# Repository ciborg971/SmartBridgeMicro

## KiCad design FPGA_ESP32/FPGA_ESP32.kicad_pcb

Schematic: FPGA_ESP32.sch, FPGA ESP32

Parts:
H1, H2, H3, H4: MountingHole_Pad; MountingHole_2.2mm_M2_Pad_Via
J1, J3, J4, J5: Conn_01x14_Female; PinHeader_1x14_P1.00mm_Vertical
R1, R2, R3, R4: 4K7; R_0201_0603Metric
U1: LFE5UM-25F-7MG285C; BGA285N50P18X18_1000X1000X130N

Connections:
+1V8: J5.2; also elsewhere on the board
/SPI_CLK: J5.8; also elsewhere on the board
/SPI_HD: J5.6; also elsewhere on the board
/SPI_MISO: J5.10; also elsewhere on the board
/SPI_MOSI: J5.9; also elsewhere on the board
/SPI_WP: J5.7; also elsewhere on the board
AVIN1: J1.2; also elsewhere on the board
AVIN2: J1.4; also elsewhere on the board
EN: J5.5; also elsewhere on the board
GND: H1.1, H2.1, H3.1, H4.1, J1.1, J1.3, J1.5, J3.2, J4.2, J5.1, J5.3; also elsewhere on the board
IO0: J1.6; also elsewhere on the board
IO1: J1.7; also elsewhere on the board
IO2: J1.8; also elsewhere on the board
IO3: J1.9; also elsewhere on the board
IO4: J1.10; also elsewhere on the board
IO5: J1.11; also elsewhere on the board
IO6: J1.12; also elsewhere on the board
IO7: J1.13; also elsewhere on the board
IO8: J1.14; also elsewhere on the board
IO9: J3.3; also elsewhere on the board
IO10: J3.4; also elsewhere on the board
IO11: J3.5; also elsewhere on the board
IO12: J3.6; also elsewhere on the board
IO13: J3.7; also elsewhere on the board
IO14: J3.8; also elsewhere on the board
IO15: J3.9; also elsewhere on the board
IO16: J3.10; also elsewhere on the board
IO17: J3.11; also elsewhere on the board
IO18: J3.12; also elsewhere on the board
IO19: J3.13; also elsewhere on the board
IO20: J3.14; also elsewhere on the board
IO21: J4.3; also elsewhere on the board
IO22: J4.4; also elsewhere on the board
IO23: J4.5; also elsewhere on the board
IO24: J4.6; also elsewhere on the board
IO25: J4.7; also elsewhere on the board
IO26: J4.8; also elsewhere on the board
IO27: J4.9; also elsewhere on the board
IO28: J4.10; also elsewhere on the board
IO29: J4.11; also elsewhere on the board
IO30: J4.12; also elsewhere on the board
IO31: J4.13, R2.1, U1.V13 (TMS); also elsewhere on the board
IO32: J4.14, R4.1, U1.V14 (TDO); also elsewhere on the board
IO33: J5.11; also elsewhere on the board
IO34: J5.12; also elsewhere on the board
IO35: J5.13; also elsewhere on the board
IO36: J5.14, R3.2, U1.T13 (TDI); also elsewhere on the board
IO37: R1.2, U1.U13 (TCK)
VIO: J3.1, J4.1, J5.4, R1.1, R2.2, R3.1, R4.2; also elsewhere on the board

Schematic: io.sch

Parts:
C1, C6, C14: 10uF; C_0402_1005Metric
C5, C11, C15, C16: 0.1uF; C_0402_1005Metric
C7, C17: C; C_0402_1005Metric
C19, C21: 1uF; C_0402_1005Metric
R5: 1M; R_0201_0603Metric
R7, R12, R13: 4.7K; R_0201_0603Metric
R14: 4K7; R_0201_0603Metric
U1: LFE5UM-25F-7MG285C; BGA285N50P18X18_1000X1000X130N
U3: LP5910-1.1BYKAT; BGA-4_2x2_0.74x0.74mm
U4, U6: W956D6KBKX; BGA-49_7x7_4.0x4.0mm
U5: TW9900; QFN-32_EP_4x4_Pitch0.4mm
U8: ADP222ACPZ-1825-R7; SON50P200X200X60-9N
Y1: Crystal_GND23; Crystal_SMD_2520-4Pin_2.5x2.0mm

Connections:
+1V8: C1.2, C5.2, C6.2, C11.2, C14.1, C15.1, U1.G5 (VCCIO2), U1.G14 (VCCIO7), U1.H5 (VCCIO2), U1.H14 (VCCIO7), U1.M14 (VCCIO6), U1.N14 (VCCIO6), U4.A1, U4.A3, U4.A5, U4.A7, U4.B4, U4.G3, U4.G5, U5.1, U5.7, U5.23, U6.A1, U6.A3, U6.A5, U6.A7, U6.B4, U6.G3, U6.G5, U8.7, U8.8; also elsewhere on the board
+2V5: U1.E6 (VCCAUX), U1.E13 (VCCAUX), U1.N6 (VCCAUX), U1.P5 (VCCAUXA0), U1.P13 (VCCAUX), U1.R3 (VCCAUXA0), U8.4, U8.5
/FPGA/DONE: U1.U15 (DONE); also elsewhere on the board
/FPGA/FPGA_CS: U1.R17 (PB13A/SN/CSN); also elsewhere on the board
/FPGA/FPGA_HOLDN: U1.U17 (PB15A/HOLDN/DI/BUSY/CSSPIN/CEN)
/FPGA/HSYNC: U1.A8 (PT35B/PCLKC1_0), U5.10
/FPGA/MPOUT: U1.N17 (PB6A/D5/MISO2/IO5), U5.11
/FPGA/RAM0_A16: U1.D18 (PL26C/PCLKT6_0), U4.G1
/FPGA/RAM0_A17: U1.F18 (PL26D/PCLKC6_0), U4.G7
/FPGA/RAM0_A18: U1.F17 (PL29A/GR_PCLK6_0), U4.F7
/FPGA/RAM0_A19: U1.F16 (PL29B), U4.E7
/FPGA/RAM0_A20: U1.F15 (PL29C/GR_PCLK6_1), U4.E1
/FPGA/RAM0_A21: U1.G16 (PL29D), U4.F1
/FPGA/RAM0_ADQ0: U1.G18 (PL32A), U4.B7
/FPGA/RAM0_ADQ1: U1.H17 (PL32B), U4.D7
/FPGA/RAM0_ADQ2: U1.G15 (PL35A), U4.C6
/FPGA/RAM0_ADQ3: U1.H15 (PL35B/VREF1_6), U4.C5
/FPGA/RAM0_ADQ4: U1.H16 (PL35C), U4.D4
/FPGA/RAM0_ADQ5: U1.J16 (PL35D), U4.B3
/FPGA/RAM0_ADQ6: U1.J18 (PL41A), U4.C2
/FPGA/RAM0_ADQ7: U1.K18 (PL41B), U4.D1
/FPGA/RAM0_ADQ8: U1.K16 (PL41C), U4.C7
/FPGA/RAM0_ADQ9: U1.K15 (PL41D), U4.B6
/FPGA/RAM0_ADQ10: U1.K17 (PL44A), U4.B5
/FPGA/RAM0_ADQ11: U1.L18 (PL44B), U4.D5
/FPGA/RAM0_ADQ12: U1.L15 (PL44C), U4.D3
/FPGA/RAM0_ADQ13: U1.L16 (PL44D), U4.C3
/FPGA/RAM0_ADQ14: U1.D17 (PL26A/PCLKT6_1), U4.B2
/FPGA/RAM0_ADQ15: U1.C18 (PL26B/PCLKC6_1), U4.C1
/FPGA/RAM0_ADV: U1.C12 (PL2A), U4.E2
/FPGA/RAM0_CE: U1.A15 (PL14D), U4.G6
/FPGA/RAM0_CLK: U1.B15 (PL20A/GR_PCLK7_1), U4.G2
/FPGA/RAM0_CRE: U1.D15 (PL17A), U4.F4
/FPGA/RAM0_LB: U1.A17 (PL23A/PCLKT7_1), U4.F6
/FPGA/RAM0_OE: U1.D16 (PL17B), U4.C4
/FPGA/RAM0_UB: U1.A12 (PL5A), U4.E6
/FPGA/RAM0_WAIT: U1.C13 (PL8B), U4.B1
/FPGA/RAM0_WE: U1.B12 (PL2B), U4.F2
/FPGA/RAM1_A16: U1.D1 (PR23D/PCLKC2_0), U6.G1
/FPGA/RAM1_A17: U1.D4 (PR14A), U6.G7
/FPGA/RAM1_A18: U1.C4 (PR14B), U6.F7
/FPGA/RAM1_A19: U1.B4 (PR14C/VREF1_2), U6.E7
/FPGA/RAM1_A20: U1.C3 (PR14D), U6.E1
/FPGA/RAM1_A21: U1.J17 (PL38C), U6.F1
/FPGA/RAM1_ADQ0: U1.A6 (PR11A), U6.B7
/FPGA/RAM1_ADQ1: U1.A4 (PR11B), U6.D7
/FPGA/RAM1_ADQ2: U1.B6 (PR8A), U6.C6
/FPGA/RAM1_ADQ3: U1.A7 (PR8B), U6.C5
/FPGA/RAM1_ADQ4: U1.D6 (PR5A), U6.D4
/FPGA/RAM1_ADQ5: U1.C6 (PR5B), U6.B3
/FPGA/RAM1_ADQ6: U1.C7 (PR2A), U6.C2
/FPGA/RAM1_ADQ7: U1.B7 (PR2B/S0_IN), U6.D1
/FPGA/RAM1_ADQ8: U1.D3 (PR17A), U6.C7
/FPGA/RAM1_ADQ9: U1.C2 (PR17B), U6.B6
/FPGA/RAM1_ADQ10: U1.A3 (PR20A/GR_PCLK2_1), U6.B5
/FPGA/RAM1_ADQ11: U1.B2 (PR20B), U6.D5
/FPGA/RAM1_ADQ12: U1.A2 (PR20C/GR_PCLK2_0), U6.D3
/FPGA/RAM1_ADQ13: U1.D2 (PR23A/PCLKT2_1), U6.C3
/FPGA/RAM1_ADQ14: U1.B1 (PR23B/PCLKC2_1), U6.B2
/FPGA/RAM1_ADQ15: U1.C1 (PR23C/PCLKT2_0), U6.C1
/FPGA/RAM1_ADV: U1.B13 (PL14A), U6.E2
/FPGA/RAM1_CE: U1.H18 (PL38D), U6.G6
/FPGA/RAM1_CLK: U1.C16 (PL20C/GR_PCLK7_0), U6.G2
/FPGA/RAM1_CRE: U1.D13 (PL8A), U6.F4
/FPGA/RAM1_LB: U1.M16 (PL47C/LLC_GPLL0T_IN), U6.F6
/FPGA/RAM1_OE: U1.A16 (PL20B), U6.C4
/FPGA/RAM1_UB: U1.M17 (PL47D/LLC_GPLL0C_IN), U6.E6
/FPGA/RAM1_WAIT: U1.C15 (PL14C/VREF1_7), U6.B1
/FPGA/RAM1_WE: U1.A13 (PL14B), U6.F2
/FPGA/TW_I2C_DAT: R13.1, U1.C8 (PT67B), U5.29
/FPGA/TW_I2C_SCK: R12.1, U1.B8 (PT67A), U5.28
/FPGA/TW_INT: U1.A9 (PT35A/PCLKT1_0), U5.32
/FPGA/TW_PWRDN: U1.C9 (PT33B/PCLKC1_1), U5.30
/FPGA/VIN_CLK: U1.A11 (PT27A/PCLKT0_1), U5.12
/FPGA/VIN_D0: U1.C10 (PT29B/PCLKC0_0), U5.22
/FPGA/VIN_D1: U1.B10 (PT29A/PCLKT0_0), U5.21
/FPGA/VIN_D2: U1.R18 (PB9B/D2/IO2), U5.20
/FPGA/VIN_D3: U1.N18 (PB9A/D3/IO3), U5.19
/FPGA/VIN_D4: U1.C11 (PT4B), U5.17
/FPGA/VIN_D5: U1.B11 (PT4A), U5.16
/FPGA/VIN_D6: U1.N16 (PB4B/D6/IO6), U5.15
/FPGA/VIN_D7: U1.N15 (PB4A/D7/IO7), U5.14
/FPGA/VSYNC: U1.M18 (PB6B/D4/MOSI2/IO4), U5.9
/FPGA/nRESET: U1.B9 (PT33A/PCLKT1_1), U5.31
/SPI_CLK: U1.U16 (CCLK/MCLK/SCK); also elsewhere on the board
/SPI_HD: U1.R16 (PB18A/WRITEN); also elsewhere on the board
/SPI_MISO: U1.T18 (PB11A/D1/MISO/IO1); also elsewhere on the board
/SPI_MOSI: U1.U18 (PB11B/D0/MOSI/IO0); also elsewhere on the board
/SPI_WP: U1.T17 (PB13B/CS1N); also elsewhere on the board
/WIFI, BT, RT/FPGA_PROGRAMN: U1.T15 (PROGRAMN); also elsewhere on the board
AVIN1: U5.3; also elsewhere on the board
AVIN2: U5.2; also elsewhere on the board
GND: C1.1, C5.1, C6.1, C7.2, C11.1, C14.2, C15.2, C16.2, C17.2, C19.2, C21.2, R5.1, R5.2, U1.B3 (GND), U1.B16 (GND), U1.E5 (GND), U1.E7 (GND), U1.E8 (GND), U1.E9 (GND), U1.E10 (GND), U1.E11 (GND), U1.E12 (GND), U1.E14 (GND), U1.F5 (GND), U1.F6 (GND), U1.F7 (GND), U1.F8 (GND), U1.F9 (GND), U1.F10 (GND), U1.F11 (GND), U1.F12 (GND), U1.F13 (GND), U1.F14 (GND), U1.G2 (GND), U1.G6 (GND), U1.G7 (GND), U1.G8 (GND), U1.G9 (GND), U1.G10 (GND), U1.G11 (GND), U1.G12 (GND), U1.G13 (GND), U1.G17 (GND), U1.H6 (GND), U1.H7 (GND), U1.H8 (GND), U1.H9 (GND), U1.H10 (GND), U1.H11 (GND), U1.H12 (GND), U1.H13 (GND), U1.J6 (GND), U1.J7 (GND), U1.J8 (GND), U1.J9 (GND), U1.J10 (GND), U1.J11 (GND), U1.J12 (GND), U1.J13 (GND), U1.K5 (GND), U1.K6 (GND), U1.K7 (GND), U1.K8 (GND), U1.K9 (GND), U1.K10 (GND), U1.K11 (GND), U1.K12 (GND), U1.K13 (GND), U1.K14 (GND), U1.L2 (GND), U1.L5 (GND), U1.L6 (GND), U1.L7 (GND), U1.L8 (GND), U1.L9 (GND), U1.L10 (GND), U1.L11 (GND), U1.L12 (GND), U1.L13 (GND), U1.L14 (GND), U1.L17 (GND), U1.M6 (GND), U1.M7 (GND), U1.M8 (GND), U1.M9 (GND), U1.M10 (GND), U1.M11 (GND), U1.M12 (GND), U1.M13 (GND), U1.N7 (GND), U1.N8 (GND), U1.N9 (GND), U1.N10 (GND), U1.N11 (GND), U1.N12 (GND), U1.P6 (GND), U1.P8 (GND), U1.P12 (GND), U1.R1 (GND), U1.R2 (GND), U1.T2 (GND), U1.T3 (GND), U1.T4 (GND), U1.T6 (GND), U1.T7 (GND), U1.T8 (GND), U1.T9 (GND), U1.T10 (GND), U1.T11 (GND), U1.T12 (GND), U1.T16 (GND), U1.U2 (GND), U1.U3 (GND), U1.U4 (GND), U1.U5 (GND), U1.U7 (GND), U1.U9 (GND), U1.U10 (GND), U1.U11 (GND), U1.U14 (CFG_0), U1.V4 (GND), U1.V7 (GND), U1.V10 (GND), U1.V15 (CFG_2), U3.B2, U4.A2, U4.A4, U4.A6, U4.D2, U4.D6, U4.E3, U4.E4, U4.E5, U4.G4, U5.4, U5.5, U5.8, U5.13, U5.24, U5.33, U6.A2, U6.A4, U6.A6, U6.D2, U6.D6, U6.E3, U6.E4, U6.E5, U6.G4, U8.3, U8.9, Y1.2, Y1.3; also elsewhere on the board
IO0: U1.F2 (PR32A); also elsewhere on the board
IO1: U1.G1 (PR32B); also elsewhere on the board
IO2: U1.M3 (PR41A); also elsewhere on the board
IO3: U1.L3 (PR41B); also elsewhere on the board
IO4: U1.K3 (PR41C); also elsewhere on the board
IO5: U1.K1 (PR41D); also elsewhere on the board
IO6: U1.K4 (PR38A); also elsewhere on the board
IO7: U1.L4 (PR38B); also elsewhere on the board
IO8: U1.N4 (PR38C); also elsewhere on the board
IO9: U1.N3 (PR38D); also elsewhere on the board
IO10: U1.K2 (PR44A); also elsewhere on the board
IO11: U1.L1 (PR44B); also elsewhere on the board
IO12: U1.M2 (PR44C); also elsewhere on the board
IO13: U1.N2 (PR44D); also elsewhere on the board
IO14: U1.J2 (PR35A); also elsewhere on the board
IO15: U1.J1 (PR35B/VREF1_3); also elsewhere on the board
IO16: U1.F1 (PR35C); also elsewhere on the board
IO17: U1.H1 (PR35D); also elsewhere on the board
IO18: U1.H3 (PR29A/GR_PCLK3_0); also elsewhere on the board
IO19: U1.G3 (PR29B); also elsewhere on the board
IO20: U1.J3 (PR29C/GR_PCLK3_1); also elsewhere on the board
IO21: U1.H2 (PR29D); also elsewhere on the board
IO22: U1.H4 (PR26A/PCLKT3_1); also elsewhere on the board
IO23: U1.G4 (PR26B/PCLKC3_1); also elsewhere on the board
IO24: U1.F4 (PR26C/PCLKT3_0); also elsewhere on the board
IO25: U1.B17 (PL23B/PCLKC7_1); also elsewhere on the board
IO26: U1.B18 (PL23C/PCLKT7_0); also elsewhere on the board
IO27: U1.C17 (PL23D/PCLKC7_0); also elsewhere on the board
unnamed: C7.1, U5.25, Y1.1
unnamed: C16.1, U5.6
unnamed: C17.1, U5.26, Y1.4
unnamed: R7.2, U1.V16 (INITN)
unnamed: R14.1, U1.T14 (CFG_1)
VIO: C19.1, R7.1, R12.2, R13.2, R14.2, U1.D7 (VCCIO1), U1.D12 (VCCIO0), U1.M5 (VCCIO3), U1.N5 (VCCIO3), U1.N13 (VCCIO8), U1.P14 (VCCIO8), U3.A1, U3.B1, U5.18, U5.27, U8.1, U8.2, U8.6; also elsewhere on the board

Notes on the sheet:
1V1 Reg
2V5 Reg
1V8 Reg

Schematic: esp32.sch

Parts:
C2, C3: 220pF; C_0402_1005Metric
C4: 2.2uF; C_0402_1005Metric
C8, C9, C18: 0.1uF; C_0402_1005Metric
C10: 1uF; C_0402_1005Metric
C12: 3.9pF; C_0402_1005Metric
C13: 2.4pF; C_0402_1005Metric
J2, J6: U_FL-R-SMT_10_; Coax_Conn_U.FL; MPN U.FL-R-SMT(10); Digi-Key_PN H9161CT-ND
L1: 1.2nH; L_0402_1005Metric
L2: 2.7N; L_0402_1005Metric
R6, R8: 10K; R_0201_0603Metric
R16, R17, R18, R19: 1K; R_0201_0603Metric
U2: ESP32-PICO-D4; QFN-48-1EP_7x7mm_P0.5mm_EP5.3x5.3mm
U7: RFX2411; QFN-20_EP_3x3_Pitch0.4mm
U10: GD25Q16CEIGR; PSON50P200X300X50-9N

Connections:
/FPGA/DONE: U2.17 (IO14); also elsewhere on the board
/FPGA/FPGA_CS: U2.18 (IO12); also elsewhere on the board
/SPI_CLK: U2.35 (IO18), U10.6; also elsewhere on the board
/SPI_HD: U2.42 (IO21); also elsewhere on the board
/SPI_MISO: U2.38 (IO19), U10.2; also elsewhere on the board
/SPI_MOSI: U2.36 (IO23), U10.5; also elsewhere on the board
/SPI_WP: U2.39 (IO22); also elsewhere on the board
/WIFI, BT, RT/FPGA_PROGRAMN: U2.21 (IO15); also elsewhere on the board
/WIFI, BT, RT/HOLD: U2.14 (IO25), U10.3
/WIFI, BT, RT/MODE: R17.2, U2.29 (SD3/IO10)
/WIFI, BT, RT/PDET: C9.1, R6.1, U2.8 (SENSOR_VN), U7.8
/WIFI, BT, RT/RXEN: R18.2, U2.12 (IO32)
/WIFI, BT, RT/SPI_FLASH_CS: U2.15 (IO26), U10.1
/WIFI, BT, RT/SWANT: R16.2, U2.28 (SD2/IO9)
/WIFI, BT, RT/TXEN: R19.2, U2.13 (IO33)
/WIFI, BT, RT/TXRX: C12.2, C13.1, U7.5
/WIFI, BT, RT/WP: U2.16 (IO27), U10.7
EN: C18.1, R8.2, U2.9 (EN); also elsewhere on the board
GND: C2.2, C3.2, C4.2, C8.2, C9.2, C10.2, C13.2, C18.2, J2.1, J6.1, L1.1, L2.2, R6.2, U2.49 (GND), U7.1, U7.11, U7.13, U7.19, U7.21, U10.4; also elsewhere on the board
IO28: U2.20 (IO13); also elsewhere on the board
IO29: U2.10 (IO34); also elsewhere on the board
IO30: U2.11 (IO35); also elsewhere on the board
IO31: U2.23 (IO0); also elsewhere on the board
IO32: U2.41 (U0TXD/IO1); also elsewhere on the board
IO33: U2.22 (IO2); also elsewhere on the board
IO34: U2.40 (U0RXD/IO3); also elsewhere on the board
IO35: U2.24 (IO4); also elsewhere on the board
IO36: U2.34 (IO5); also elsewhere on the board
unnamed: C12.1, L2.1, U2.2 (LNA_IN)
unnamed: J2.2, U7.14
unnamed: J6.2, U7.12
unnamed: L1.2, U7.15
unnamed: R16.1, U7.10
unnamed: R17.1, U7.9
unnamed: R18.1, U7.7
unnamed: R19.1, U7.6
VIO: C2.1, C3.1, C4.1, C8.1, C10.1, R8.1, U2.1 (VDDA), U2.3 (VDDA3P3), U2.4 (VDDA3P3), U2.19 (VDD3P3_RTC), U2.37 (VDD3P3_CPU), U2.43 (VDDA), U2.46 (VDDA), U7.18, U7.20, U10.8; also elsewhere on the board

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
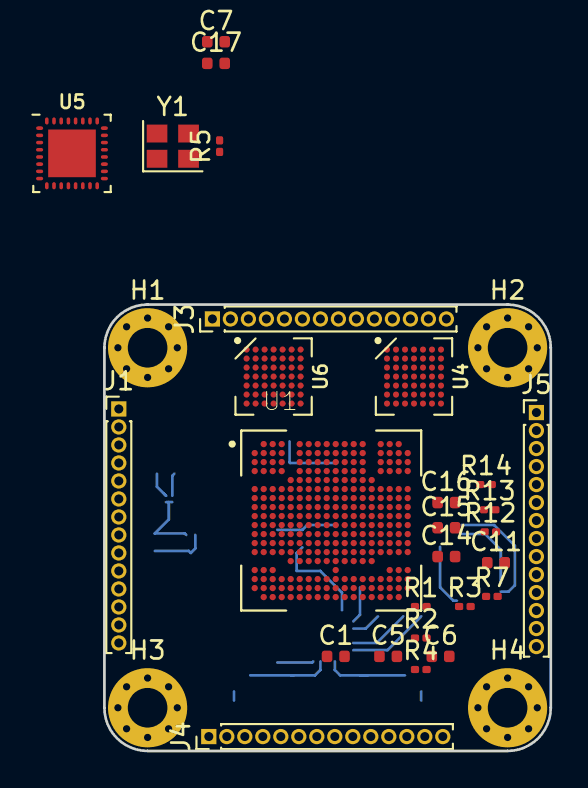
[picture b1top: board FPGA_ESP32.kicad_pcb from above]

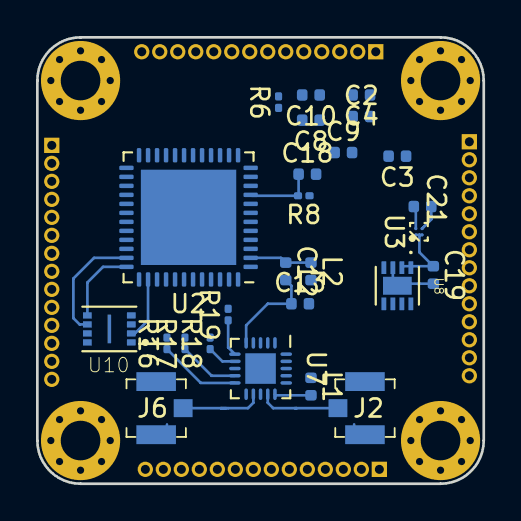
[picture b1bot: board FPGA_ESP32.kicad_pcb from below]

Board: 4 copper layers, 24.8 x 24.8 mm, 57 parts (26 on the bottom side), 155 nets.

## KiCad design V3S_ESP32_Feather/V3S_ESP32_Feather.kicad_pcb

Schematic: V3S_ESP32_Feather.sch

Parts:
J1: USB_B_Micro; JST_SH_BM05B-SRSS-TB_1x05-1MP_P1.00mm_Vertical
J10: UART; JST_SH_SM04B-SRSS-TB_1x04-1MP_P1.00mm_Horizontal
MH1, MH2, MH3, MH4: MountingHole_Pad; MountingHole_2.5mm_Pad_Via
TP4: CPU_RST; TestPoint_Pad_D1.0mm

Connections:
+3V3: J10.4; also elsewhere on the board
/RST: TP4.1; also elsewhere on the board
/UART_RX_D0: J10.2; also elsewhere on the board
/UART_TX_D0: J10.3; also elsewhere on the board
/USB_D_N: J1.3; also elsewhere on the board
/USB_D_P: J1.2; also elsewhere on the board
/USB_ID: J1.5; also elsewhere on the board
GND: J1.1, J10.1, MH1.1, MH2.1, MH3.1, MH4.1; also elsewhere on the board
VBUS: J1.4; also elsewhere on the board

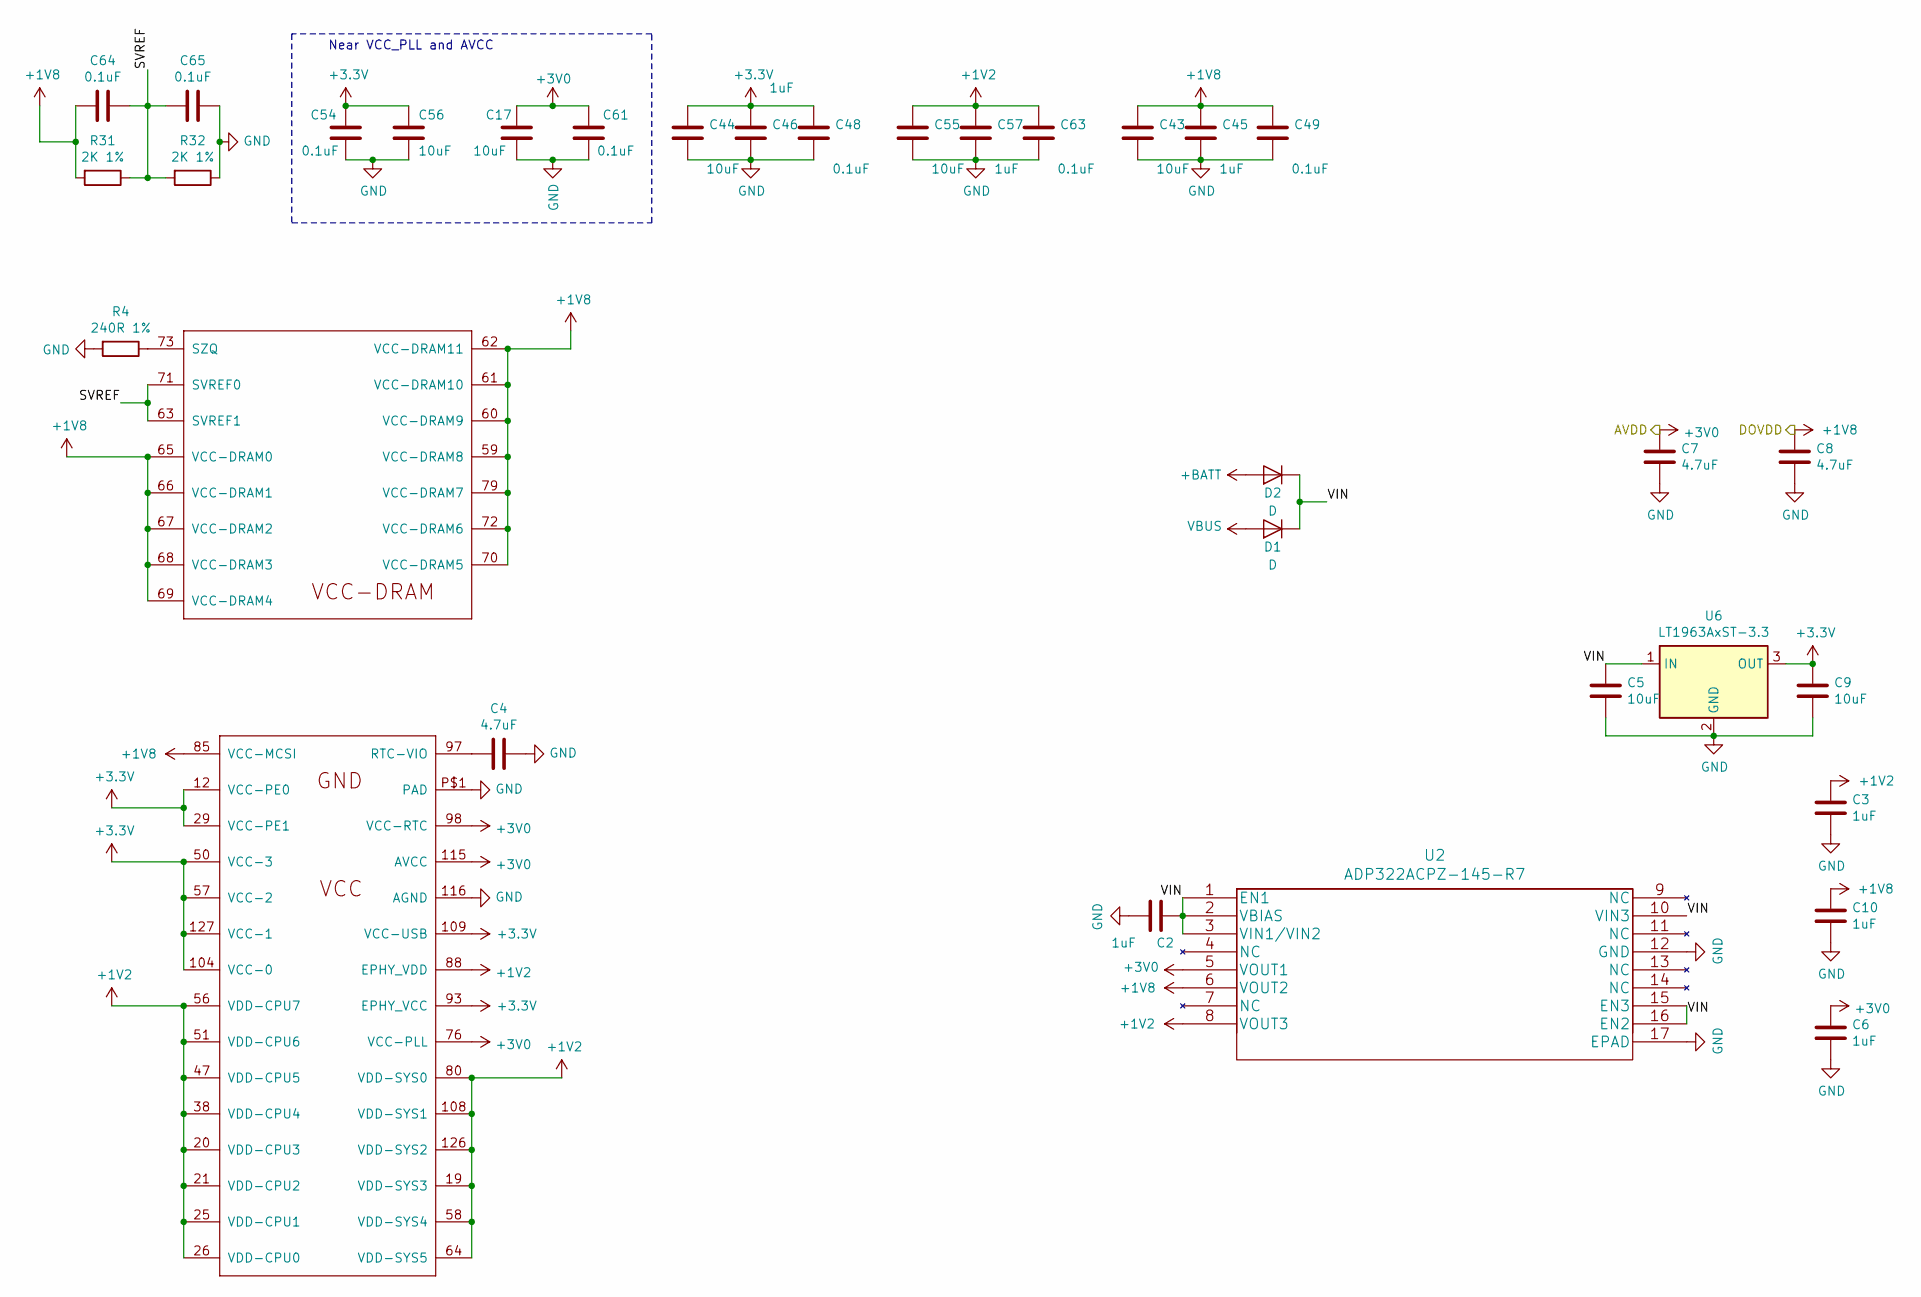
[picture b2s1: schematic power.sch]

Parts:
C2, C3, C6, C10, C45, C46, C57: 1uF; C_0201_0603Metric
C4, C7, C8: 4.7uF; C_0201_0603Metric
C5, C9, C17, C43, C44, C55, C56: 10uF; C_0402_1005Metric
C48, C49, C54, C61, C63, C64, C65: 0.1uF; C_0201_0603Metric
D1, D2: D; D_0201_0603Metric
R4: 240R 1%; R_0201_0603Metric
R31, R32: 2K 1%; R_0201_0603Metric
U1: V3S; LQFP-128_14x14mm_P0.4mm
U2: ADP322ACPZ-145-R7; QFN50P300X300X90-17N
U6: LT1963AxST-3.3; SOT-223-3_TabPin2

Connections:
+1V2: C3.1, C55.1, C57.1, C63.1, U1.19 (VDD-SYS3), U1.20 (VDD-CPU3), U1.21 (VDD-CPU2), U1.25 (VDD-CPU1), U1.26 (VDD-CPU0), U1.38 (VDD-CPU4), U1.47 (VDD-CPU5), U1.51 (VDD-CPU6), U1.56 (VDD-CPU7), U1.58 (VDD-SYS4), U1.64 (VDD-SYS5), U1.80 (VDD-SYS0), U1.88 (EPHY_VDD), U1.108 (VDD-SYS1), U1.126 (VDD-SYS2), U2.8 (VOUT3)
+1V8: C8.1, C10.1, C43.1, C45.1, C49.1, C64.2, R31.2, U1.59 (VCC-DRAM8), U1.60 (VCC-DRAM9), U1.61 (VCC-DRAM10), U1.62 (VCC-DRAM11), U1.65 (VCC-DRAM0), U1.66 (VCC-DRAM1), U1.67 (VCC-DRAM2), U1.68 (VCC-DRAM3), U1.69 (VCC-DRAM4), U1.70 (VCC-DRAM5), U1.72 (VCC-DRAM6), U1.79 (VCC-DRAM7), U1.85 (VCC-MCSI), U2.6 (VOUT2); also elsewhere on the board
+3V0: C6.1, C7.1, C17.2, C61.2, U1.76 (VCC-PLL), U1.98 (VCC-RTC), U1.115 (AVCC), U2.5 (VOUT1); also elsewhere on the board
+3V3: C9.1, C44.1, C46.1, C48.1, C54.1, C56.1, U1.12 (VCC-PE0), U1.29 (VCC-PE1), U1.50 (VCC-3), U1.57 (VCC-2), U1.93 (EPHY_VCC), U1.104 (VCC-0), U1.109 (VCC-USB), U1.127 (VCC-1), U6.3 (OUT); also elsewhere on the board
+BATT: D2.2 (A); also elsewhere on the board
/PMIC Power Battery/SVREF: C64.1, C65.2, R31.1, R32.2, U1.63 (SVREF1), U1.71 (SVREF0)
/PMIC Power Battery/VIN: C2.1, C5.1, D1.1 (K), D2.1 (K), U2.1 (EN1), U2.2 (VBIAS), U2.3 (VIN1/VIN2), U2.10 (VIN3), U2.15 (EN3), U2.16 (EN2), U6.1 (IN)
GND: C2.2, C3.2, C4.1, C5.2, C6.2, C7.2, C8.2, C9.2, C10.2, C17.1, C43.2, C44.2, C45.2, C46.2, C48.2, C49.2, C54.2, C55.2, C56.2, C57.2, C61.1, C63.2, C65.1, R4.2, R32.1, U1.116 (AGND), U1.P$1 (PAD), U2.12 (GND), U2.17 (EPAD), U6.2 (GND); also elsewhere on the board
unnamed: C4.2, U1.97 (RTC-VIO)
unnamed: R4.1, U1.73 (SZQ)
VBUS: D1.2 (A); also elsewhere on the board

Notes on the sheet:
Near VCC_PLL and AVCC

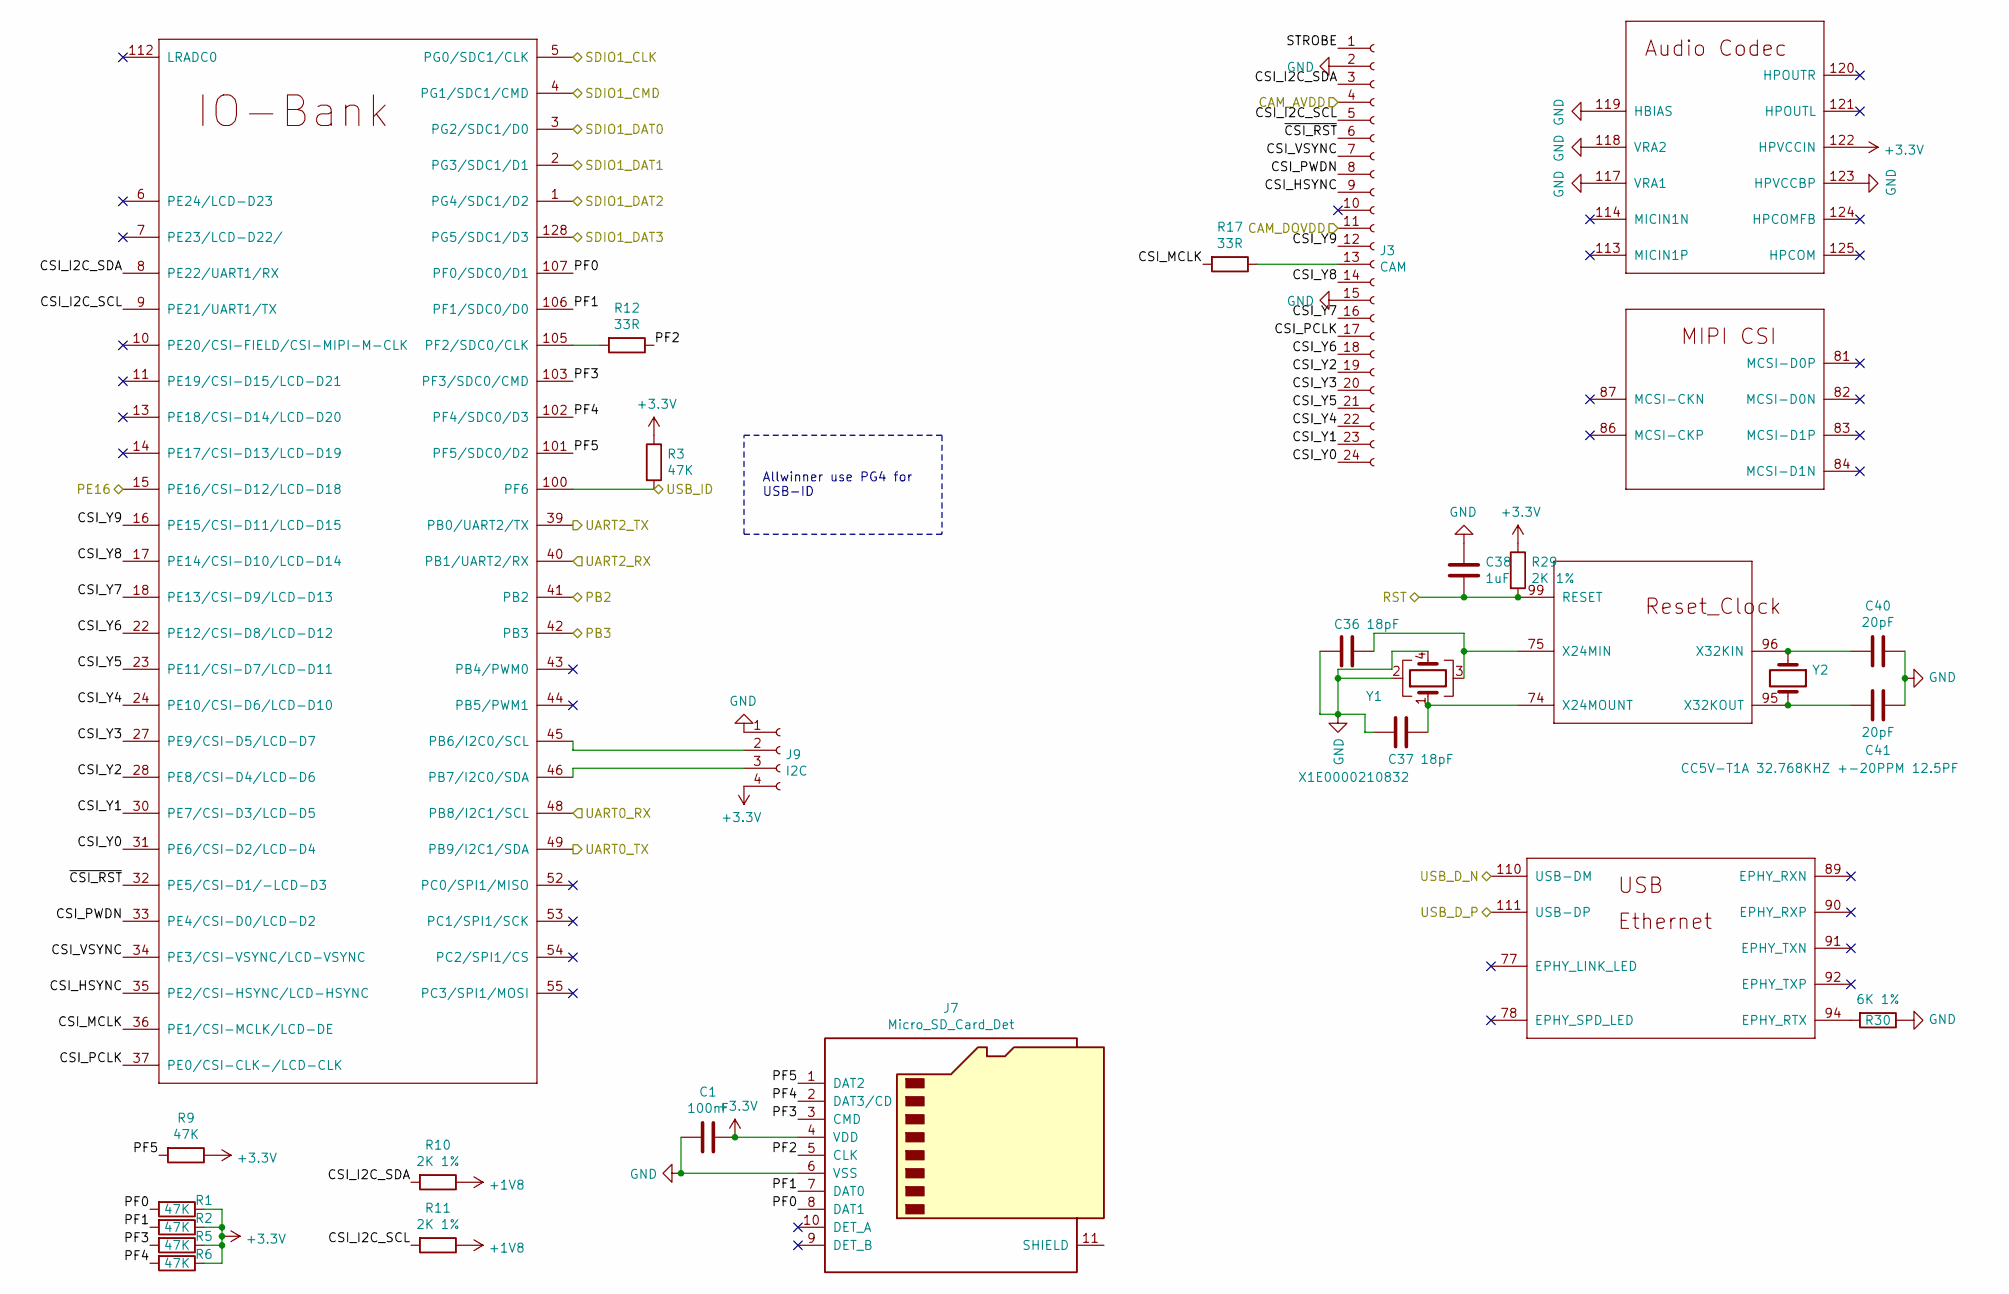
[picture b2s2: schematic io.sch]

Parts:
C1: 100nF; C_0201_0603Metric
C36, C37: 18pF; C_0201_0603Metric
C38: 1uF; C_0201_0603Metric
C40, C41: 20pF; C_0201_0603Metric
J3: CAM; FPC_24_CAM
J7: Micro_SD_Card_Det; microSD_HC_Hirose_DM3D-SF
J9: I2C; JST_SH_SM04B-SRSS-TB_1x04-1MP_P1.00mm_Horizontal
R1, R2, R3, R5, R6, R9: 47K; R_0201_0603Metric
R10, R11, R29: 2K 1%; R_0201_0603Metric
R12, R17: 33R; R_0201_0603Metric
R30: 6K 1%; R_0201_0603Metric
U1: V3S; LQFP-128_14x14mm_P0.4mm
Y1: X1E0000210832; Crystal_SMD_3225-4Pin_3.2x2.5mm
Y2: CC5V-T1A 32.768KHZ +-20PPM 12.5PF; SOIC-2

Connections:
+1V8: J3.11, R10.1, R11.1; also elsewhere on the board
+3V0: J3.4; also elsewhere on the board
+3V3: C1.1, J7.4 (VDD), J9.4, R1.1, R2.1, R3.1, R5.1, R6.1, R9.1, R29.1, U1.122 (HPVCCIN); also elsewhere on the board
/All V3s input output/CSI_HSYNC: J3.9, U1.35 (PE2/CSI-HSYNC/LCD-HSYNC)
/All V3s input output/CSI_I2C_SCL: J3.5, R11.2, U1.9 (PE21/UART1/TX)
/All V3s input output/CSI_I2C_SDA: J3.3, R10.2, U1.8 (PE22/UART1/RX)
/All V3s input output/CSI_MCLK: R17.2, U1.36 (PE1/CSI-MCLK/LCD-DE)
/All V3s input output/CSI_PCLK: J3.17, U1.37 (PE0/CSI-CLK-/LCD-CLK)
/All V3s input output/CSI_PWDN: J3.8, U1.33 (PE4/CSI-D0/LCD-D2)
/All V3s input output/CSI_VSYNC: J3.7, U1.34 (PE3/CSI-VSYNC/LCD-VSYNC)
/All V3s input output/CSI_Y0: J3.24, U1.31 (PE6/CSI-D2/LCD-D4)
/All V3s input output/CSI_Y1: J3.23, U1.30 (PE7/CSI-D3/LCD-D5)
/All V3s input output/CSI_Y2: J3.19, U1.28 (PE8/CSI-D4/LCD-D6)
/All V3s input output/CSI_Y3: J3.20, U1.27 (PE9/CSI-D5/LCD-D7)
/All V3s input output/CSI_Y4: J3.22, U1.24 (PE10/CSI-D6/LCD-D10)
/All V3s input output/CSI_Y5: J3.21, U1.23 (PE11/CSI-D7/LCD-D11)
/All V3s input output/CSI_Y6: J3.18, U1.22 (PE12/CSI-D8/LCD-D12)
/All V3s input output/CSI_Y7: J3.16, U1.18 (PE13/CSI-D9/LCD-D13)
/All V3s input output/CSI_Y8: J3.14, U1.17 (PE14/CSI-D10/LCD-D14)
/All V3s input output/CSI_Y9: J3.12, U1.16 (PE15/CSI-D11/LCD-D15)
/All V3s input output/PF0: J7.8 (DAT1), R1.2, U1.107 (PF0/SDC0/D1)
/All V3s input output/PF1: J7.7 (DAT0), R2.2, U1.106 (PF1/SDC0/D0)
/All V3s input output/PF2: J7.5 (CLK), R12.1
/All V3s input output/PF3: J7.3 (CMD), R5.2, U1.103 (PF3/SDC0/CMD)
/All V3s input output/PF4: J7.2 (DAT3/CD), R6.2, U1.102 (PF4/SDC0/D3)
/All V3s input output/PF5: J7.1 (DAT2), R9.2, U1.101 (PF5/SDC0/D2)
/All V3s input output/SDIO1_CLK: U1.5 (PG0/SDC1/CLK); also elsewhere on the board
/All V3s input output/SDIO1_CMD: U1.4 (PG1/SDC1/CMD); also elsewhere on the board
/All V3s input output/SDIO1_DAT0: U1.3 (PG2/SDC1/D0); also elsewhere on the board
/All V3s input output/SDIO1_DAT1: U1.2 (PG3/SDC1/D1); also elsewhere on the board
/All V3s input output/SDIO1_DAT2: U1.1 (PG4/SDC1/D2); also elsewhere on the board
/All V3s input output/SDIO1_DAT3: U1.128 (PG5/SDC1/D3); also elsewhere on the board
/All V3s input output/~CSI_RST: J3.6, U1.32 (PE5/CSI-D1/-LCD-D3)
/RST: C38.2, R29.2, U1.99 (RESET); also elsewhere on the board
/UART_RX_D0: U1.48 (PB8/I2C1/SCL); also elsewhere on the board
/UART_TX_D0: U1.49 (PB9/I2C1/SDA); also elsewhere on the board
/USB_D_N: U1.110 (USB-DM); also elsewhere on the board
/USB_D_P: U1.111 (USB-DP); also elsewhere on the board
/USB_ID: R3.2, U1.100 (PF6); also elsewhere on the board
/WIFI, BT, RT/EN: U1.42 (PB3); also elsewhere on the board
/WIFI, BT, RT/IO0_PULL: U1.41 (PB2); also elsewhere on the board
/WIFI, BT, RT/IO2_PULL: U1.15 (PE16/CSI-D12/LCD-D18); also elsewhere on the board
/WIFI, BT, RT/UART0_RX: U1.39 (PB0/UART2/TX); also elsewhere on the board
/WIFI, BT, RT/UART0_TX: U1.40 (PB1/UART2/RX); also elsewhere on the board
GND: C1.2, C36.2, C37.2, C38.1, C40.1, C41.1, J3.2, J3.15, J7.6 (VSS), J9.1, R30.1, U1.117 (VRA1), U1.118 (VRA2), U1.119 (HBIAS), U1.123 (HPVCCBP), Y1.2, Y1.4; also elsewhere on the board
unnamed: C36.1, U1.75 (X24MIN), Y1.3
unnamed: C37.1, U1.74 (X24MOUNT), Y1.1
unnamed: C40.2, U1.96 (X32KIN), Y2.1
unnamed: C41.2, U1.95 (X32KOUT), Y2.2
unnamed: J3.13, R17.1
unnamed: J9.2, U1.45 (PB6/I2C0/SCL)
unnamed: J9.3, U1.46 (PB7/I2C0/SDA)
unnamed: R12.2, U1.105 (PF2/SDC0/CLK)
unnamed: R30.2, U1.94 (EPHY_RTX)

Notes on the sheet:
Allwinner use PG4 for USB-ID

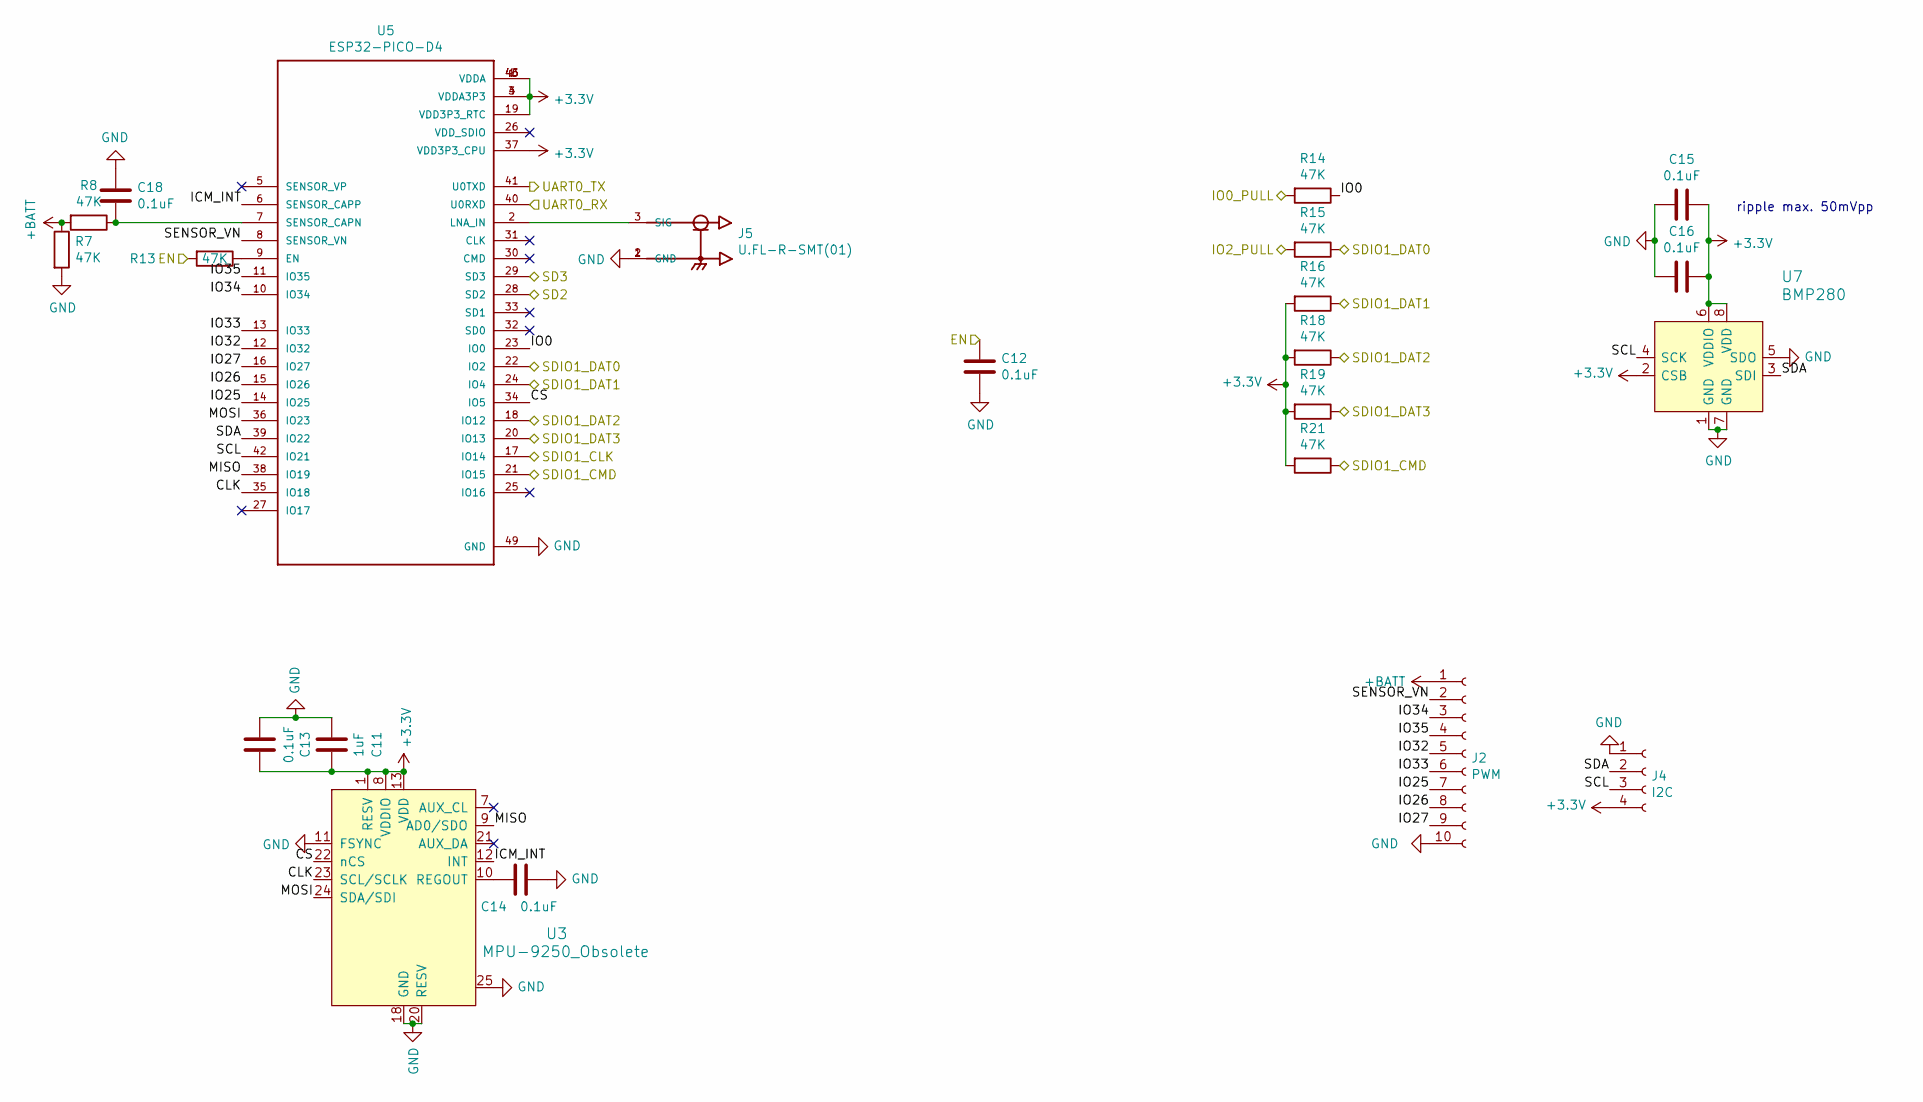
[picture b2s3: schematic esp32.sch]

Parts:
C11: 1uF; C_0201_0603Metric
C12, C13, C14, C15, C16, C18: 0.1uF; C_0201_0603Metric
J2: PWM; JST_SH_SM10B-SRSS-TB_1x10-1MP_P1.00mm_Horizontal
J4: I2C; JST_SH_SM04B-SRSS-TB_1x04-1MP_P1.00mm_Horizontal
J5: U.FL-R-SMT(01); HRS_U.FL-R-SMT(01)
R7, R8, R13, R14, R15, R16, R18, R19, R21: 47K; R_0201_0603Metric
U3: MPU-9250_Obsolete; QFN-24-1EP_3x3mm; MPN MPU-9250; Digi-Key_PN 1428-1019-1-ND
U5: ESP32-PICO-D4; PQFN50P700X700X104-49N
U7: BMP280; LGA-8_2x2.5mm_BMP280; MPN BMP280; Digi-Key_PN 828-1064-1-ND

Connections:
+3V3: C11.1, C13.1, C15.1, C16.1, J4.4, R16.2, R18.2, R19.2, R21.2, U3.1 (RESV), U3.8 (VDDIO), U3.13 (VDD), U5.1 (VDDA), U5.3 (VDDA3P3), U5.4 (VDDA3P3), U5.19 (VDD3P3_RTC), U5.37 (VDD3P3_CPU), U5.43 (VDDA), U5.46 (VDDA), U7.2 (CSB), U7.6 (VDDIO), U7.8 (VDD); also elsewhere on the board
+BATT: J2.1, R7.1, R8.2; also elsewhere on the board
/All V3s input output/SDIO1_CLK: U5.17 (IO14); also elsewhere on the board
/All V3s input output/SDIO1_CMD: R21.1, U5.21 (IO15); also elsewhere on the board
/All V3s input output/SDIO1_DAT0: R15.1, U5.22 (IO2); also elsewhere on the board
/All V3s input output/SDIO1_DAT1: R16.1, U5.24 (IO4); also elsewhere on the board
/All V3s input output/SDIO1_DAT2: R18.1, U5.18 (IO12); also elsewhere on the board
/All V3s input output/SDIO1_DAT3: R19.1, U5.20 (IO13); also elsewhere on the board
/WIFI, BT, RT/CLK: U3.23 (SCL/SCLK), U5.35 (IO18)
/WIFI, BT, RT/CS: U3.22 (nCS), U5.34 (IO5)
/WIFI, BT, RT/EN: C12.1, R13.2; also elsewhere on the board
/WIFI, BT, RT/ICM_INT: U3.12 (INT), U5.6 (SENSOR_CAPP)
/WIFI, BT, RT/IO0: R14.1, U5.23 (IO0)
/WIFI, BT, RT/IO0_PULL: R14.2; also elsewhere on the board
/WIFI, BT, RT/IO2_PULL: R15.2; also elsewhere on the board
/WIFI, BT, RT/IO25: J2.7, U5.14 (IO25)
/WIFI, BT, RT/IO26: J2.8, U5.15 (IO26)
/WIFI, BT, RT/IO27: J2.9, U5.16 (IO27)
/WIFI, BT, RT/IO32: J2.5, U5.12 (IO32)
/WIFI, BT, RT/IO33: J2.6, U5.13 (IO33)
/WIFI, BT, RT/IO34: J2.3, U5.10 (IO34)
/WIFI, BT, RT/IO35: J2.4, U5.11 (IO35)
/WIFI, BT, RT/MISO: U3.9 (AD0/SDO), U5.38 (IO19)
/WIFI, BT, RT/MOSI: U3.24 (SDA/SDI), U5.36 (IO23)
/WIFI, BT, RT/SCL: J4.3, U5.42 (IO21), U7.4 (SCK)
/WIFI, BT, RT/SDA: J4.2, U5.39 (IO22), U7.3 (SDI)
/WIFI, BT, RT/SENSOR_VN: J2.2, U5.8 (SENSOR_VN)
/WIFI, BT, RT/UART0_RX: U5.40 (U0RXD); also elsewhere on the board
/WIFI, BT, RT/UART0_TX: U5.41 (U0TXD); also elsewhere on the board
GND: C11.2, C12.2, C13.2, C14.1, C15.2, C16.2, C18.2, J2.10, J4.1, J5.1 (GND), J5.2 (GND), R7.2, U3.11 (FSYNC), U3.18 (GND), U3.20 (RESV), U3.25, U5.49 (GND), U7.1 (GND), U7.5 (SDO), U7.7 (GND); also elsewhere on the board
unnamed: C14.2, U3.10 (REGOUT)
unnamed: C18.1, R8.1, U5.7 (SENSOR_CAPN)
unnamed: J5.3 (SIG), U5.2 (LNA_IN)
unnamed: R13.1, U5.9 (EN)

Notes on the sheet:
ripple max. 50mVpp

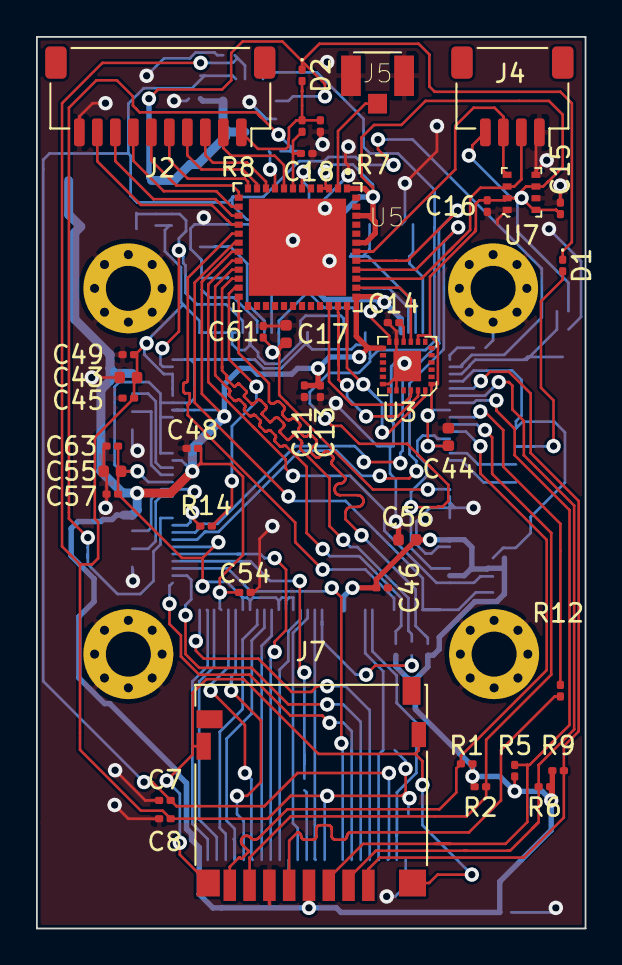
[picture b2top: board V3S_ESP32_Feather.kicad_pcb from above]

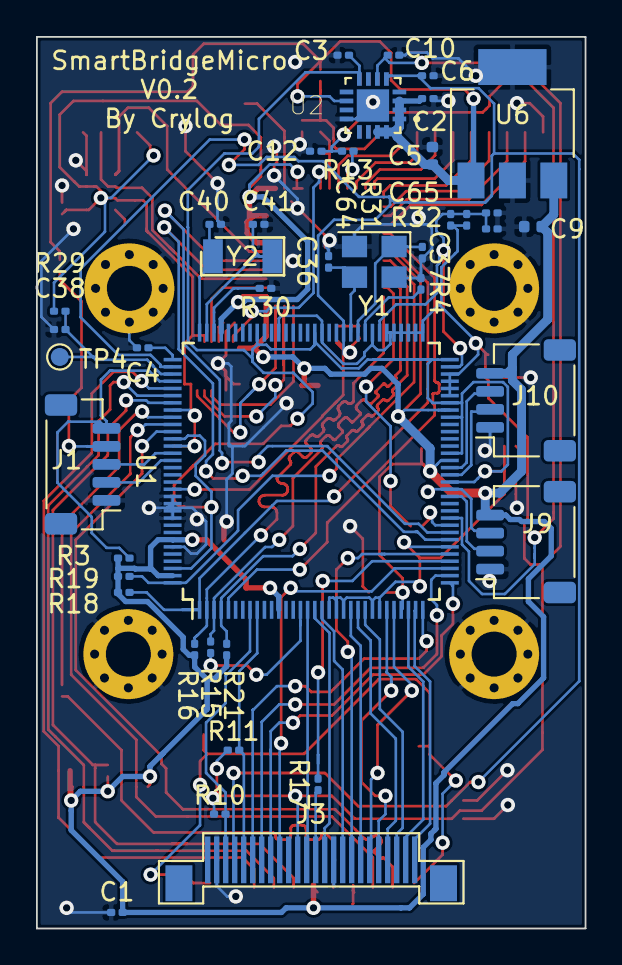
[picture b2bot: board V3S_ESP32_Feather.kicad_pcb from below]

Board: 2 copper layers, 30.5 x 49.5 mm, 84 parts (41 on the bottom side), 81 nets.
